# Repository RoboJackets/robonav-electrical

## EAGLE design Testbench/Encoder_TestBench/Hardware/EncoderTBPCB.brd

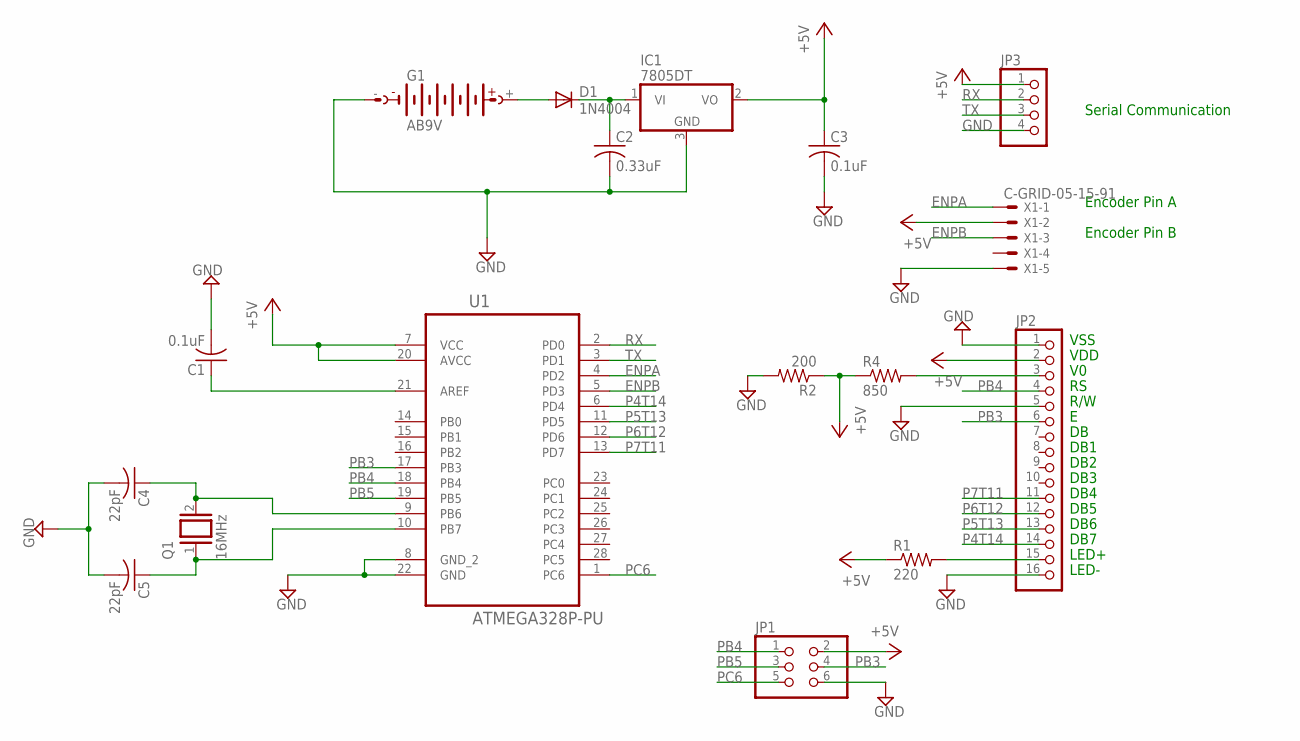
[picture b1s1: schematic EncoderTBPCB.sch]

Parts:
C1, C3: 0.1uF; C0603
C2: 0.33uF; C0603
C4, C5: 22pF; C0603
D1: 1N4004; DO41-10
G1: AB9V
IC1: 7805DT; TO252
JP1: PINHD-2X3; 2X03
JP2: PINHD-1X16; 1X16
JP3: PINHD-1X4; 1X04
Q1: 16MHz; QS
R1: 220; R0603
R2: 200; R0603
R4: 850; R0603
U1: ATMEGA328P-PU; DIP254P762X457-28
X1: C-GRID-05-15-91; 15-91-05

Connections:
CRYSTAL: C4.1, Q1.2, U1.9 (PB6)
ENPA: U1.4 (PD2), X1.1
ENPB: U1.5 (PD3), X1.3
GND: C1.2, C2.2, C3.2, C4.2, C5.2, G1.-, IC1.3 (GND), JP1.6, JP2.1, JP2.5, JP2.16, JP3.4, R2.2, U1.8 (GND_2), U1.22 (GND), X1.5
unnamed: JP2.15, R1.2
unnamed: C5.1, Q1.1, U1.10 (PB7)
unnamed: C1.1, U1.21 (AREF)
unnamed: D1.A, G1.+
unnamed: C2.1, D1.C, IC1.1 (VI)
P4T14: JP2.14, U1.6 (PD4)
P5T13: JP2.13, U1.11 (PD5)
P6T12: JP2.12, U1.12 (PD6)
P7T11: JP2.11, U1.13 (PD7)
PB3: JP1.4, JP2.6, U1.17 (PB3)
PB4: JP1.1, JP2.4, U1.18 (PB4)
PB5: JP1.3, U1.19 (PB5)
PC6: JP1.5, U1.1 (PC6)
RX: JP3.2, U1.2 (PD0)
TX: JP3.3, U1.3 (PD1)
VDD: C3.1, IC1.2 (VO), JP1.2, JP2.2, JP3.1, R1.1, R2.1, R4.1, U1.7 (VCC), U1.20 (AVCC), X1.2
VO: JP2.3, R4.2

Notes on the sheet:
VSS
VDD
R/W
DB1
DB2
DB3
DB4
DB5
DB6
DB7
LED+
LED-
Encoder Pin A
Encoder Pin B
Serial Communication

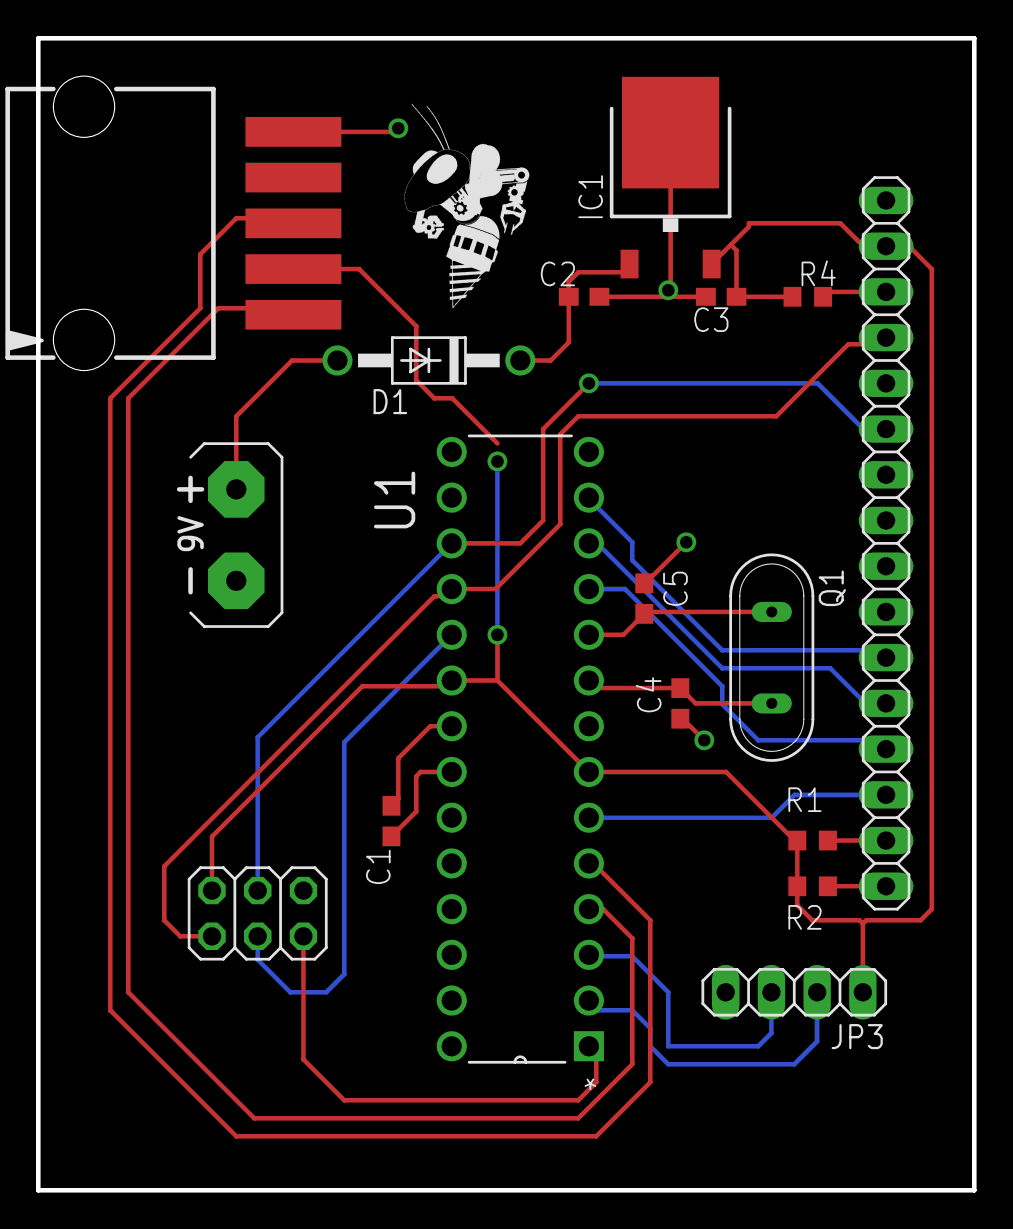
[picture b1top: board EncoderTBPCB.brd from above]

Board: 2 copper layers, 52.0 x 64.0 mm, 18 parts (0 on the bottom side), 21 nets.

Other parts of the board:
U$1: ROBOBUZZ_0.6X

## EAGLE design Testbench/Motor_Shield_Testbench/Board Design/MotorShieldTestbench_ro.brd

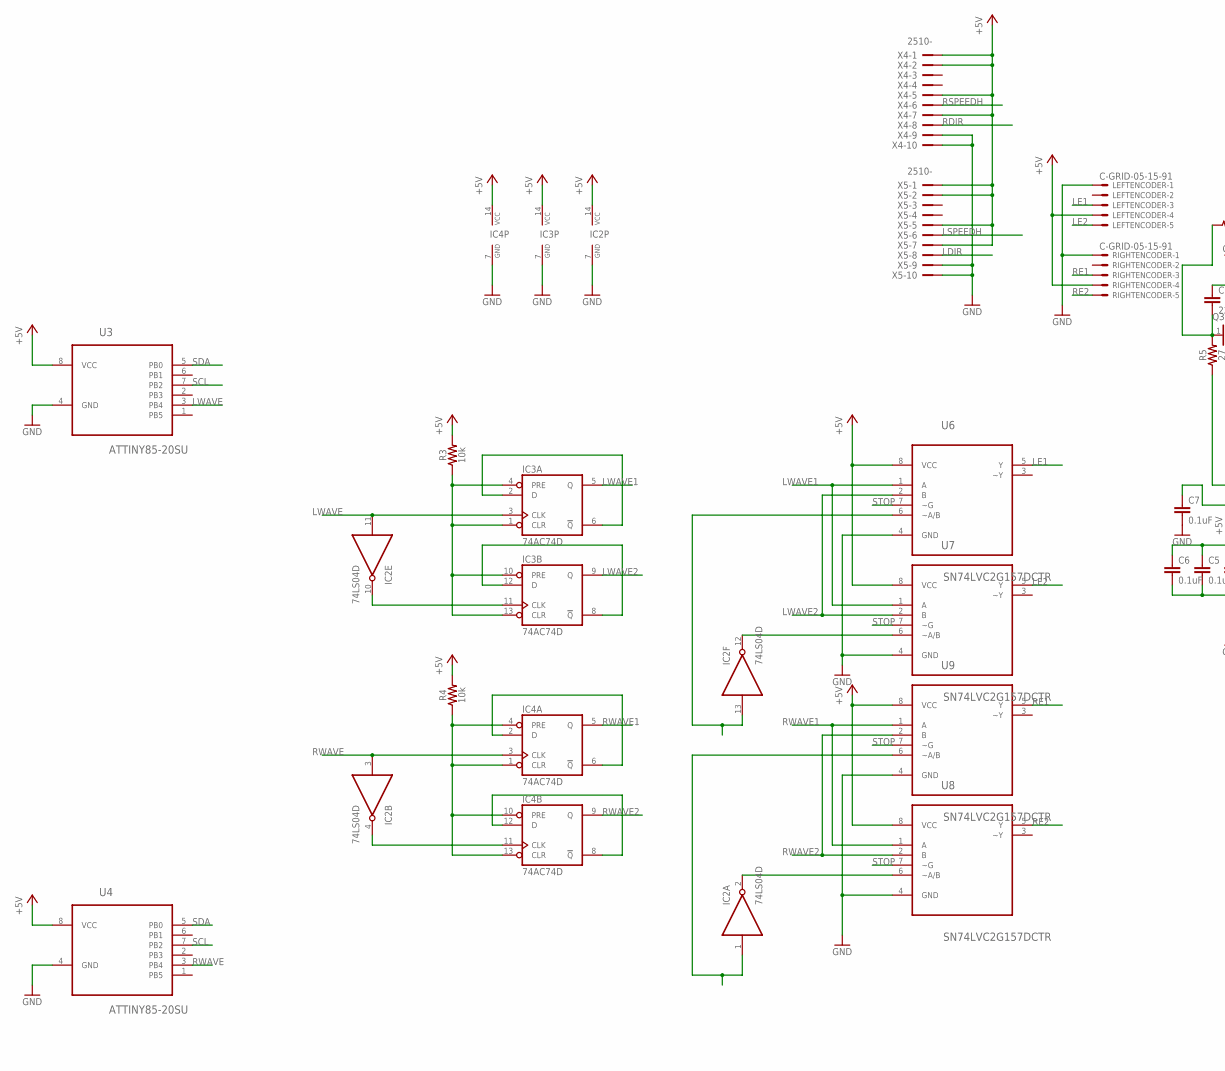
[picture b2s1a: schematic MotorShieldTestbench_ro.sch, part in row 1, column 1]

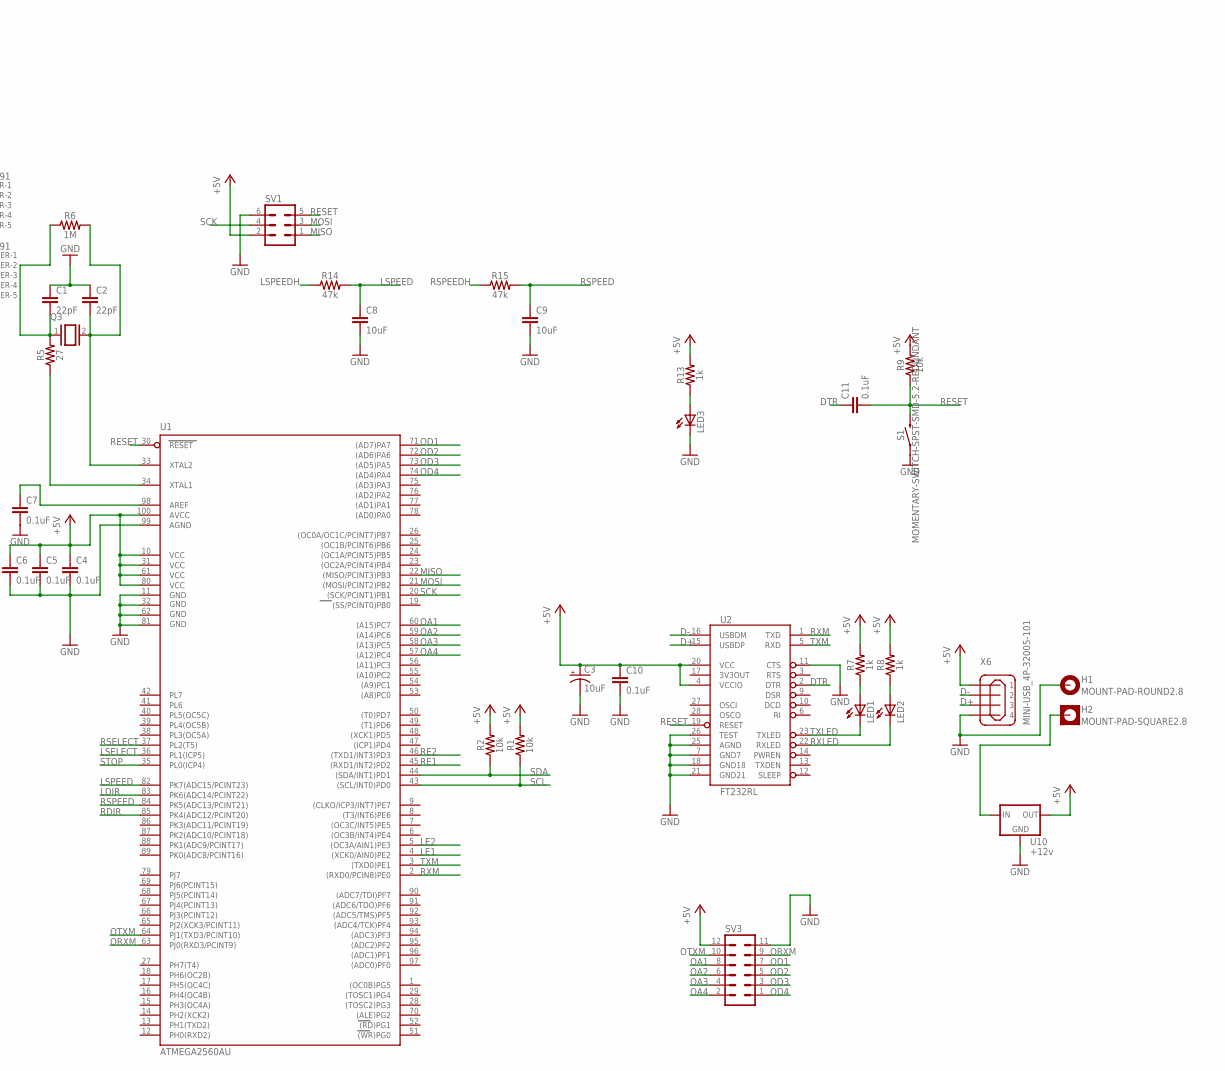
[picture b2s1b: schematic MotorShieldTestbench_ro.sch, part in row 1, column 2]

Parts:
C1, C2: 22pF; 0603
C3: 10uF; 0603-POLAR
C4, C5, C6, C7, C11: 0.1uF; 0603
C8, C9: 10uF; 0603
C10: 0.1uF; 0402
H1: MOUNT-PAD-ROUND2.8; 2,8-PAD
H2: MOUNT-PAD-SQUARE2.8; 2,8-PAD-SQUARE
IC2: 74LS04D; SO14
IC3, IC4: 74AC74D; SO14
LED1, LED2, LED3: LED_E; LED_1206
LEFTENCODER: C-GRID-05-15-91; 15-91-05
Q3: XTAL/S; QS
R1, R2, R3, R4, R9: 10k; 0603
R5: 27; 0603
R6: 1M; 0603
R7, R8, R13: 1k; 0603
R14, R15: 47k; 0603
RIGHTENCODER: C-GRID-05-15-91; 15-91-05
S1: MOMENTARY-SWITCH-SPST-SMD-5.2-REDUNDANT; TACTILE_SWITCH_SMD_5.2MM
SV1: MA03-2
SV3: MA06-2
U1: ATMEGA2560AU; TQFP100
U2: FT232RL; SSOP28DB
U3, U4: ATTINY85-20SU; SOIC127P798X216-8N
U6, U7, U8, U9: SN74LVC2G157DCTR; SOP65P400X130-8N
U10: +12v; TO-252
X4, X5: 2510-; PAK100/2500-10
X6: MINI-USB_4P-32005-101; 32005-101

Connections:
+5V: C3.+, C4.1, C5.1, C6.1, C10.1, IC2.14 (VCC), IC3.14 (VCC), IC4.14 (VCC), LEFTENCODER.4, R1.2, R2.2, R3.2, R4.2, R7.2, R8.2, R9.2, R13.2, RIGHTENCODER.4, SV1.2, SV3.12, U1.10 (VCC), U1.31 (VCC1), U1.61 (VCC2), U1.80 (VCC3), U1.100 (AVCC), U2.4 (VCCIO), U2.20 (VCC), U3.8 (VCC), U4.8 (VCC), U6.8 (VCC), U7.8 (VCC), U8.8 (VCC), U9.8 (VCC), U10.2 (OUT), X4.1, X4.2, X4.5, X4.7, X5.1, X5.2, X5.5, X5.7, X6.1
D+: U2.15 (USBDP), X6.3
D-: U2.16 (USBDM), X6.2
DTR: C11.1, U2.2 (DTR)
GND: C1.1, C2.1, C3.-, C4.2, C5.2, C6.2, C7.2, C8.2, C9.2, C10.2, H1.B2,8, IC2.7 (GND), IC3.7 (GND), IC4.7 (GND), LED3.C, LEFTENCODER.1, RIGHTENCODER.1, S1.1, S1.2 (1), SV1.6, SV3.11, U1.11 (GND), U1.32 (GND1), U1.62 (GND2), U1.81 (GND3), U1.99 (AGND), U2.7 (GND7), U2.11 (CTS), U2.18 (GND18), U2.21 (GND21), U2.25 (AGND), U2.26 (TEST), U3.4 (GND), U4.4 (GND), U6.4 (GND), U7.4 (GND), U8.4 (GND), U9.4 (GND), U10.3 (GND), X4.9, X4.10, X5.9, X5.10, X6.4
LDIR: U1.83 (PK6(ADC14/PCINT22)), X5.8
LE1: LEFTENCODER.3, U1.4 ((XCK0/AIN0)PE2), U6.5 (Y)
LE2: LEFTENCODER.5, U1.5 ((OC3A/AIN1)PE3), U7.5 (Y)
LSELECT: IC2.13 (I), U1.36 (PL1(ICP5)), U6.6 (~A/B)
LSPEED: C8.1, R14.2, U1.82 (PK7(ADC15/PCINT23))
LSPEEDH: R14.1, X5.6
LWAVE: IC2.11 (I), IC3.3 (CLK), U3.3 (PB4)
LWAVE1: IC3.5 (Q), U6.1 (A), U7.1 (A)
LWAVE2: IC3.9 (Q), U6.2 (B), U7.2 (B)
MISO: SV1.1, U1.22 ((MISO/PCINT3)PB3)
MOSI: SV1.3, U1.21 ((MOSI/PCINT2)PB2)
unnamed: IC3.2 (D), IC3.6 (!Q)
unnamed: IC2.2 (O), U8.6 (~A/B)
unnamed: IC3.8 (!Q), IC3.12 (D)
unnamed: IC4.2 (D), IC4.6 (!Q)
unnamed: IC4.8 (!Q), IC4.12 (D)
unnamed: IC2.12 (O), U7.6 (~A/B)
unnamed: IC4.1 (CLR), IC4.4 (PRE), IC4.10 (PRE), IC4.13 (CLR), R4.1
unnamed: IC3.1 (CLR), IC3.4 (PRE), IC3.10 (PRE), IC3.13 (CLR), R3.1
unnamed: IC2.4 (O), IC4.11 (CLK)
unnamed: R5.1, U1.34 (XTAL1)
unnamed: C2.2, Q3.2, R6.2, U1.33 (XTAL2)
unnamed: IC2.10 (O), IC3.11 (CLK)
unnamed: H2.B2,8, U10.1 (IN)
unnamed: C7.1, U1.98 (AREF)
unnamed: LED1.A, R7.1
unnamed: LED2.A, R8.1
unnamed: LED3.A, R13.1
unnamed: C1.2, Q3.1, R5.2, R6.1
OA1: SV3.8, U1.60 ((A15)PC7)
OA2: SV3.6, U1.59 ((A14)PC6)
OA3: SV3.4, U1.58 ((A13)PC5)
OA4: SV3.2, U1.57 ((A12)PC4)
OD1: SV3.7, U1.71 ((AD7)PA7)
OD2: SV3.5, U1.72 ((AD6)PA6)
OD3: SV3.3, U1.73 ((AD5)PA5)
OD4: SV3.1, U1.74 ((AD4)PA4)
ORXM: SV3.9, U1.63 (PJ0(RXD3/PCINT9))
OTXM: SV3.10, U1.64 (PJ1(TXD3/PCINT10))
RDIR: U1.85 (PK4(ADC12/PCINT20)), X4.8
RE1: RIGHTENCODER.3, U1.45 ((RXD1/INT2)PD2), U9.5 (Y)
RE2: RIGHTENCODER.5, U1.46 ((TXD1/INT3)PD3), U8.5 (Y)
RESET: C11.2, R9.1, S1.3 (2), S1.4 (2), SV1.5, U1.30 (RESET), U2.19 (RESET)
RSELECT: IC2.1 (I), U1.37 (PL2(T5)), U9.6 (~A/B)
RSPEED: C9.1, R15.2, U1.84 (PK5(ADC13/PCINT21))
RSPEEDH: R15.1, X4.6
RWAVE: IC2.3 (I), IC4.3 (CLK), U4.3 (PB4)
RWAVE1: IC4.5 (Q), U8.1 (A), U9.1 (A)
RWAVE2: IC4.9 (Q), U8.2 (B), U9.2 (B)
RXLED: LED2.C, U2.22 (RXLED)
RXM: U1.2 ((RXD0/PCIN8)PE0), U2.1 (TXD)
SCK: SV1.4, U1.20 ((SCK/PCINT1)PB1)
SCL: R1.1, U1.43 ((SCL/INT0)PD0), U3.7 (PB2), U4.7 (PB2)
SDA: R2.1, U1.44 ((SDA/INT1)PD1), U3.5 (PB0), U4.5 (PB0)
STOP: U1.35 (PL0(ICP4)), U6.7 (~G), U7.7 (~G), U8.7 (~G), U9.7 (~G)
TXLED: LED1.C, U2.23 (TXLED)
TXM: U1.3 ((TXD0)PE1), U2.5 (RXD)

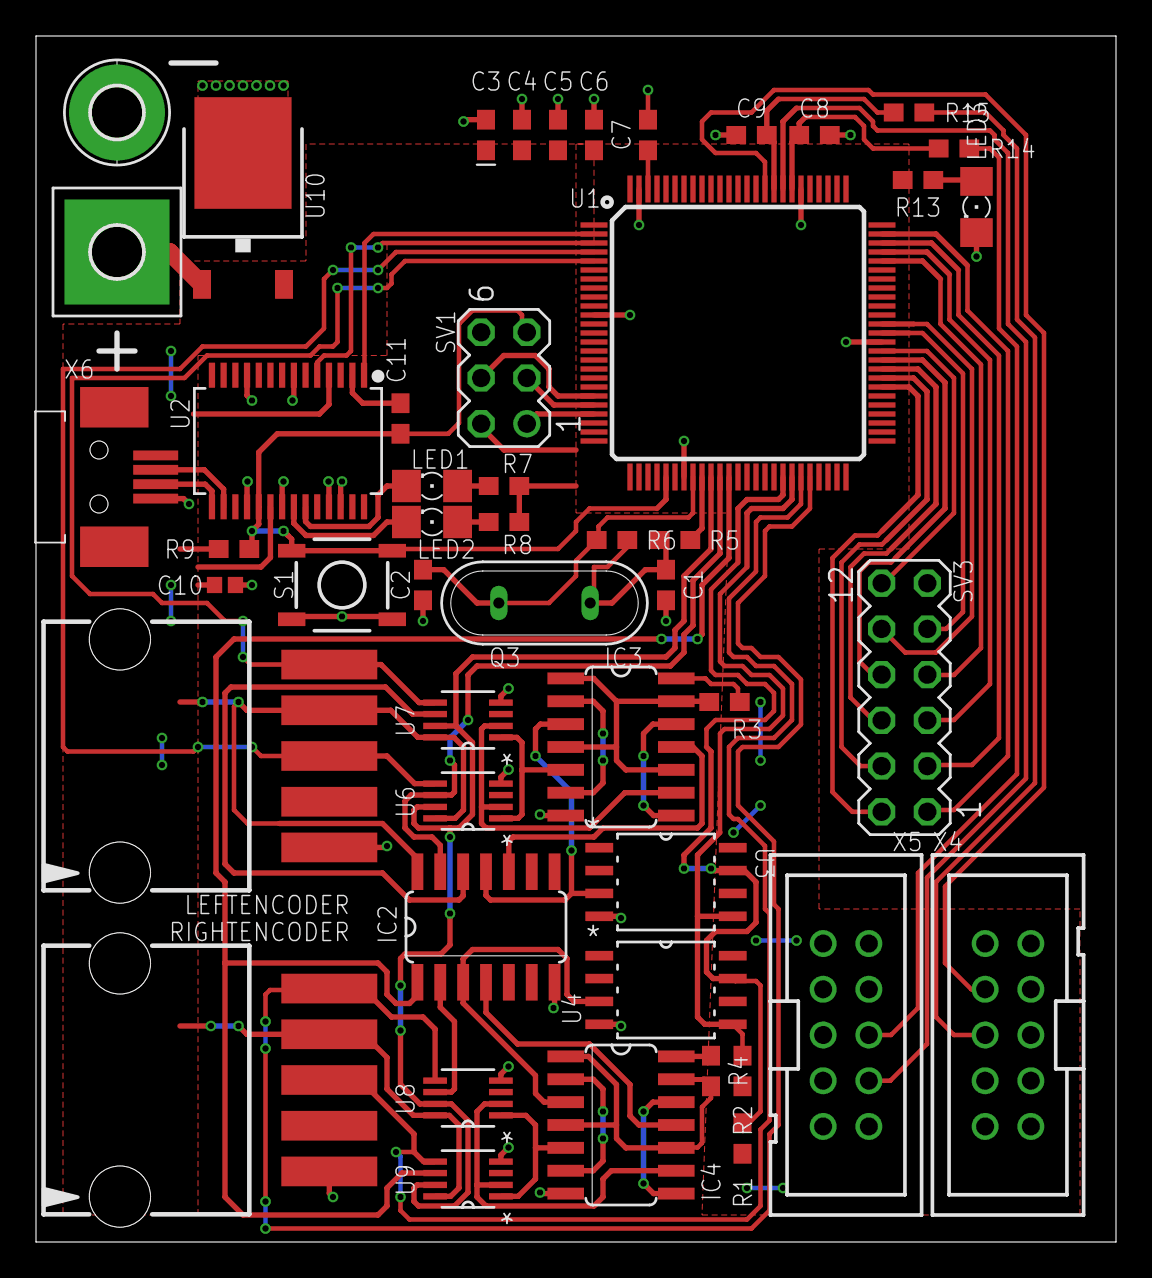
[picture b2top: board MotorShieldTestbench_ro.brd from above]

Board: 2 copper layers, 60.0 x 67.0 mm, 49 parts (0 on the bottom side), 62 nets.

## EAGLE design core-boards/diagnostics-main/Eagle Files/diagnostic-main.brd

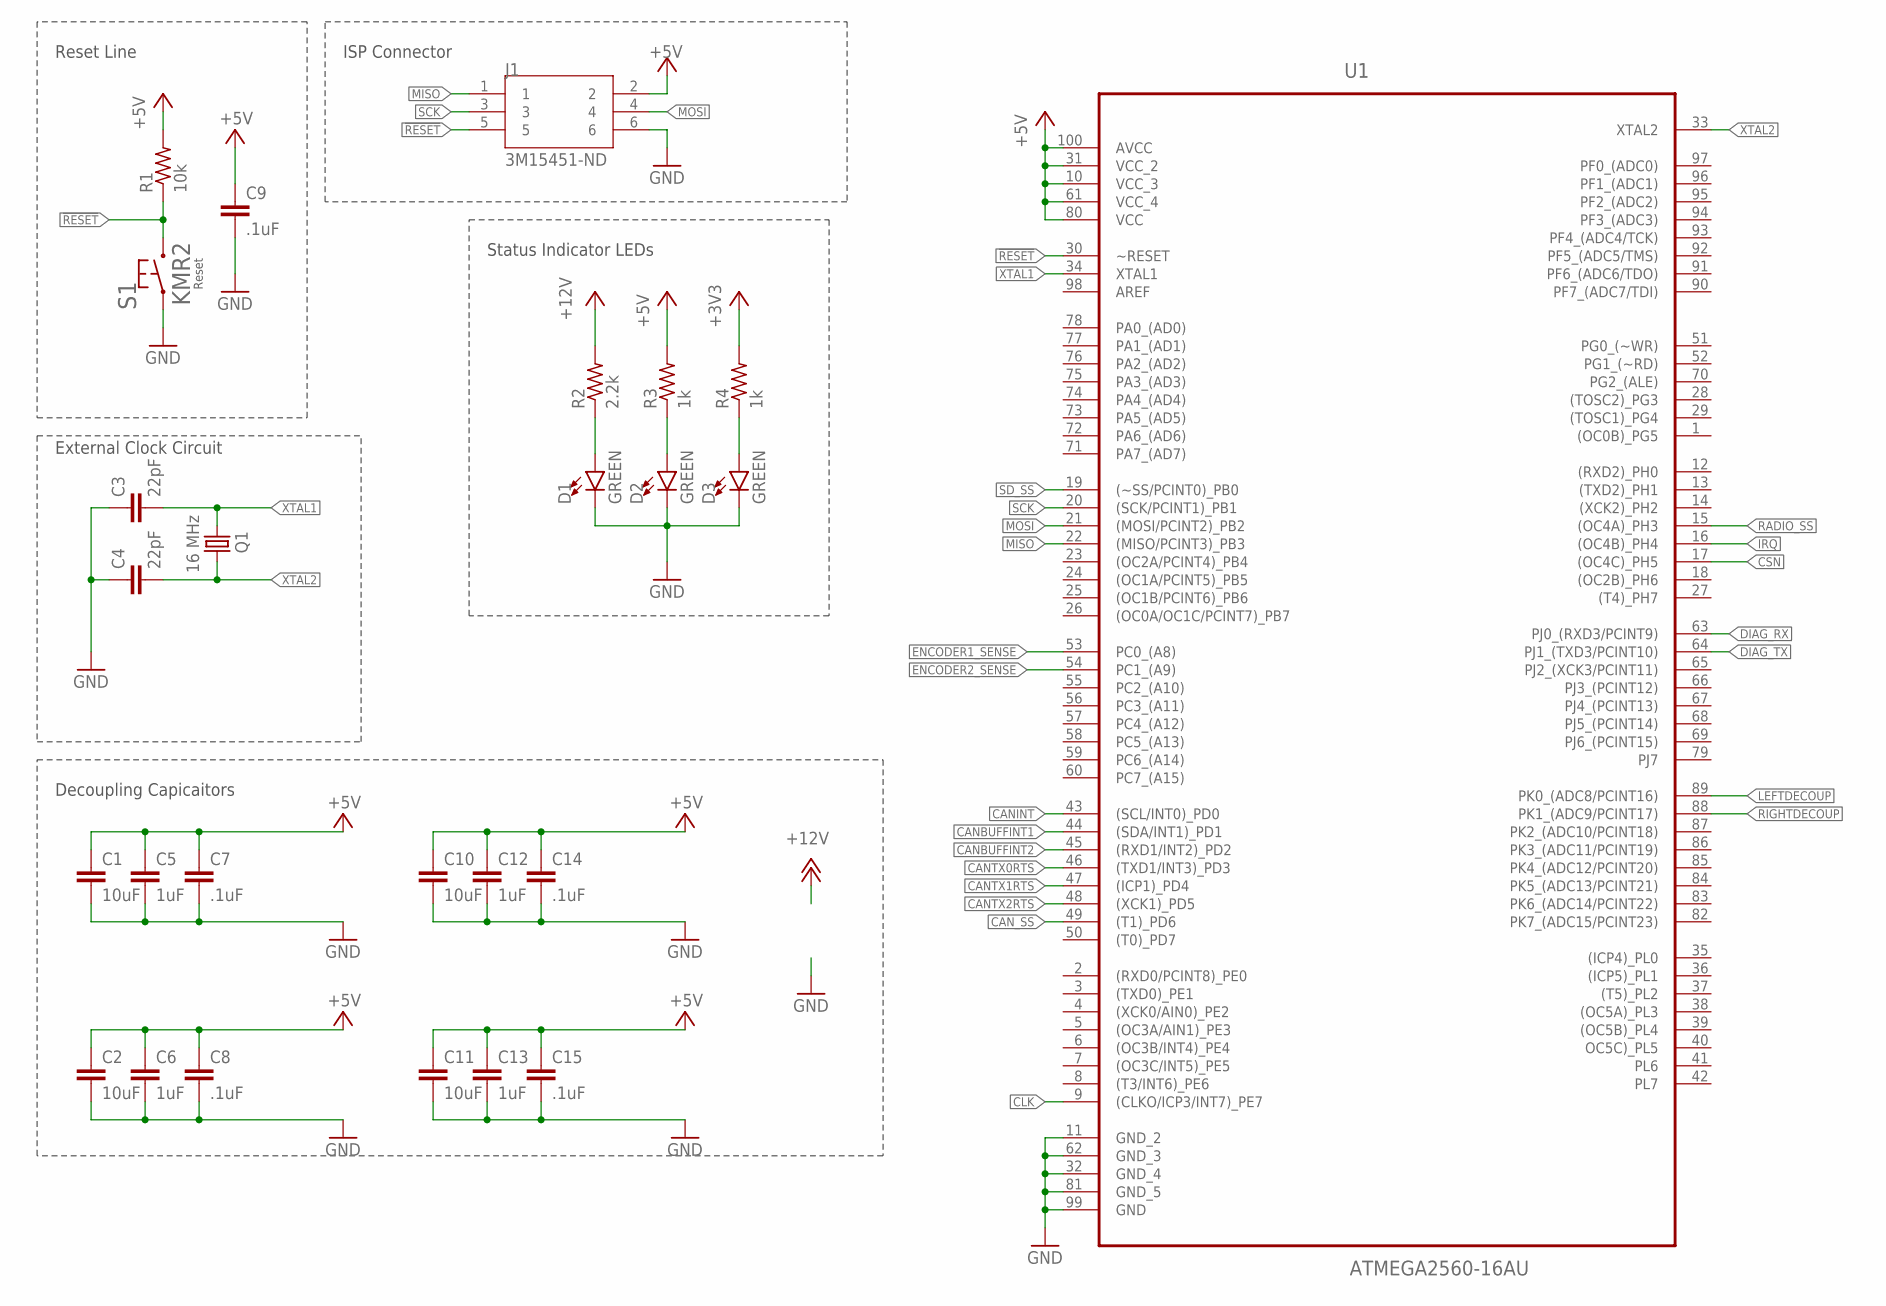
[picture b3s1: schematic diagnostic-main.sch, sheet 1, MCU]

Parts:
C1, C2, C10, C11: 10uF; C0805
C3, C4: 22pF; C0603
C5, C6, C12, C13: 1uF; C0603
C7, C8, C9, C14, C15: .1uF; C0603
D1, D2, D3: GREEN; LED-0603
J1: 3M15451-ND; 3M_30306-6002HB
Q1: 16 MHz; CSM-7X-DU
R1: 10k; R0603
R2: 2.2k; R0603
R3, R4: 1k; R0603
S1: KMR2
U1: ATMEGA2560-16AU; QFP50P1600X1600X120-100N

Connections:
3V3_LED_R: D3.A, R4.1
5V_LED_R: D2.A, R3.1
12V_LED_R: D1.A, R2.1
!RESET: J1.5, R1.1, S1.2.1 (2), S1.2.2 (2), U1.30 (~RESET)
+3V3: R4.2; also elsewhere on the board
+5V: C1.1, C2.1, C5.1, C6.1, C7.1, C8.1, C9.1, C10.1, C11.1, C12.1, C13.1, C14.1, C15.1, J1.2, R1.2, R3.2, U1.10 (VCC_3), U1.31 (VCC_2), U1.61 (VCC_4), U1.80 (VCC), U1.100 (AVCC); also elsewhere on the board
+12V: R2.2; also elsewhere on the board
CANBUFFINT1: U1.44 ((SDA/INT1)_PD1); also elsewhere on the board
CANBUFFINT2: U1.45 ((RXD1/INT2)_PD2); also elsewhere on the board
CANINT: U1.43 ((SCL/INT0)_PD0); also elsewhere on the board
CANTX0RTS: U1.46 ((TXD1/INT3)_PD3); also elsewhere on the board
CANTX1RTS: U1.47 ((ICP1)_PD4); also elsewhere on the board
CANTX2RTS: U1.48 ((XCK1)_PD5); also elsewhere on the board
CAN_SS: U1.49 ((T1)_PD6); also elsewhere on the board
CLK: U1.9 ((CLKO/ICP3/INT7)_PE7); also elsewhere on the board
CSN: U1.17 ((OC4C)_PH5); also elsewhere on the board
DIAG_RX: U1.63 (PJ0_(RXD3/PCINT9)); also elsewhere on the board
DIAG_TX: U1.64 (PJ1_(TXD3/PCINT10)); also elsewhere on the board
ENCODER1_SENSE: U1.53 (PC0_(A8)); also elsewhere on the board
ENCODER2_SENSE: U1.54 (PC1_(A9)); also elsewhere on the board
GND: C1.2, C2.2, C3.1, C4.1, C5.2, C6.2, C7.2, C8.2, C9.2, C10.2, C11.2, C12.2, C13.2, C14.2, C15.2, D1.C, D2.C, D3.C, J1.6, S1.1.1 (1), S1.1.2 (1), U1.11 (GND_2), U1.32 (GND_4), U1.62 (GND_3), U1.81 (GND_5), U1.99 (GND); also elsewhere on the board
IRQ: U1.16 ((OC4B)_PH4); also elsewhere on the board
LEFTDECOUP: U1.89 (PK0_(ADC8/PCINT16)); also elsewhere on the board
MISO: J1.1, U1.22 ((MISO/PCINT3)_PB3); also elsewhere on the board
MOSI: J1.4, U1.21 ((MOSI/PCINT2)_PB2); also elsewhere on the board
RADIO_SS: U1.15 ((OC4A)_PH3); also elsewhere on the board
RIGHTDECOUP: U1.88 (PK1_(ADC9/PCINT17)); also elsewhere on the board
SCK: J1.3, U1.20 ((SCK/PCINT1)_PB1); also elsewhere on the board
SD_SS: U1.19 ((~SS/PCINT0)_PB0); also elsewhere on the board
XTAL1: C3.2, Q1.1, U1.34 (XTAL1)
XTAL2: C4.2, Q1.2, U1.33 (XTAL2)

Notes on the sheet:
Reset Line
External Clock Circuit
Decoupling Capicaitors
ISP Connector
Status Indicator LEDs

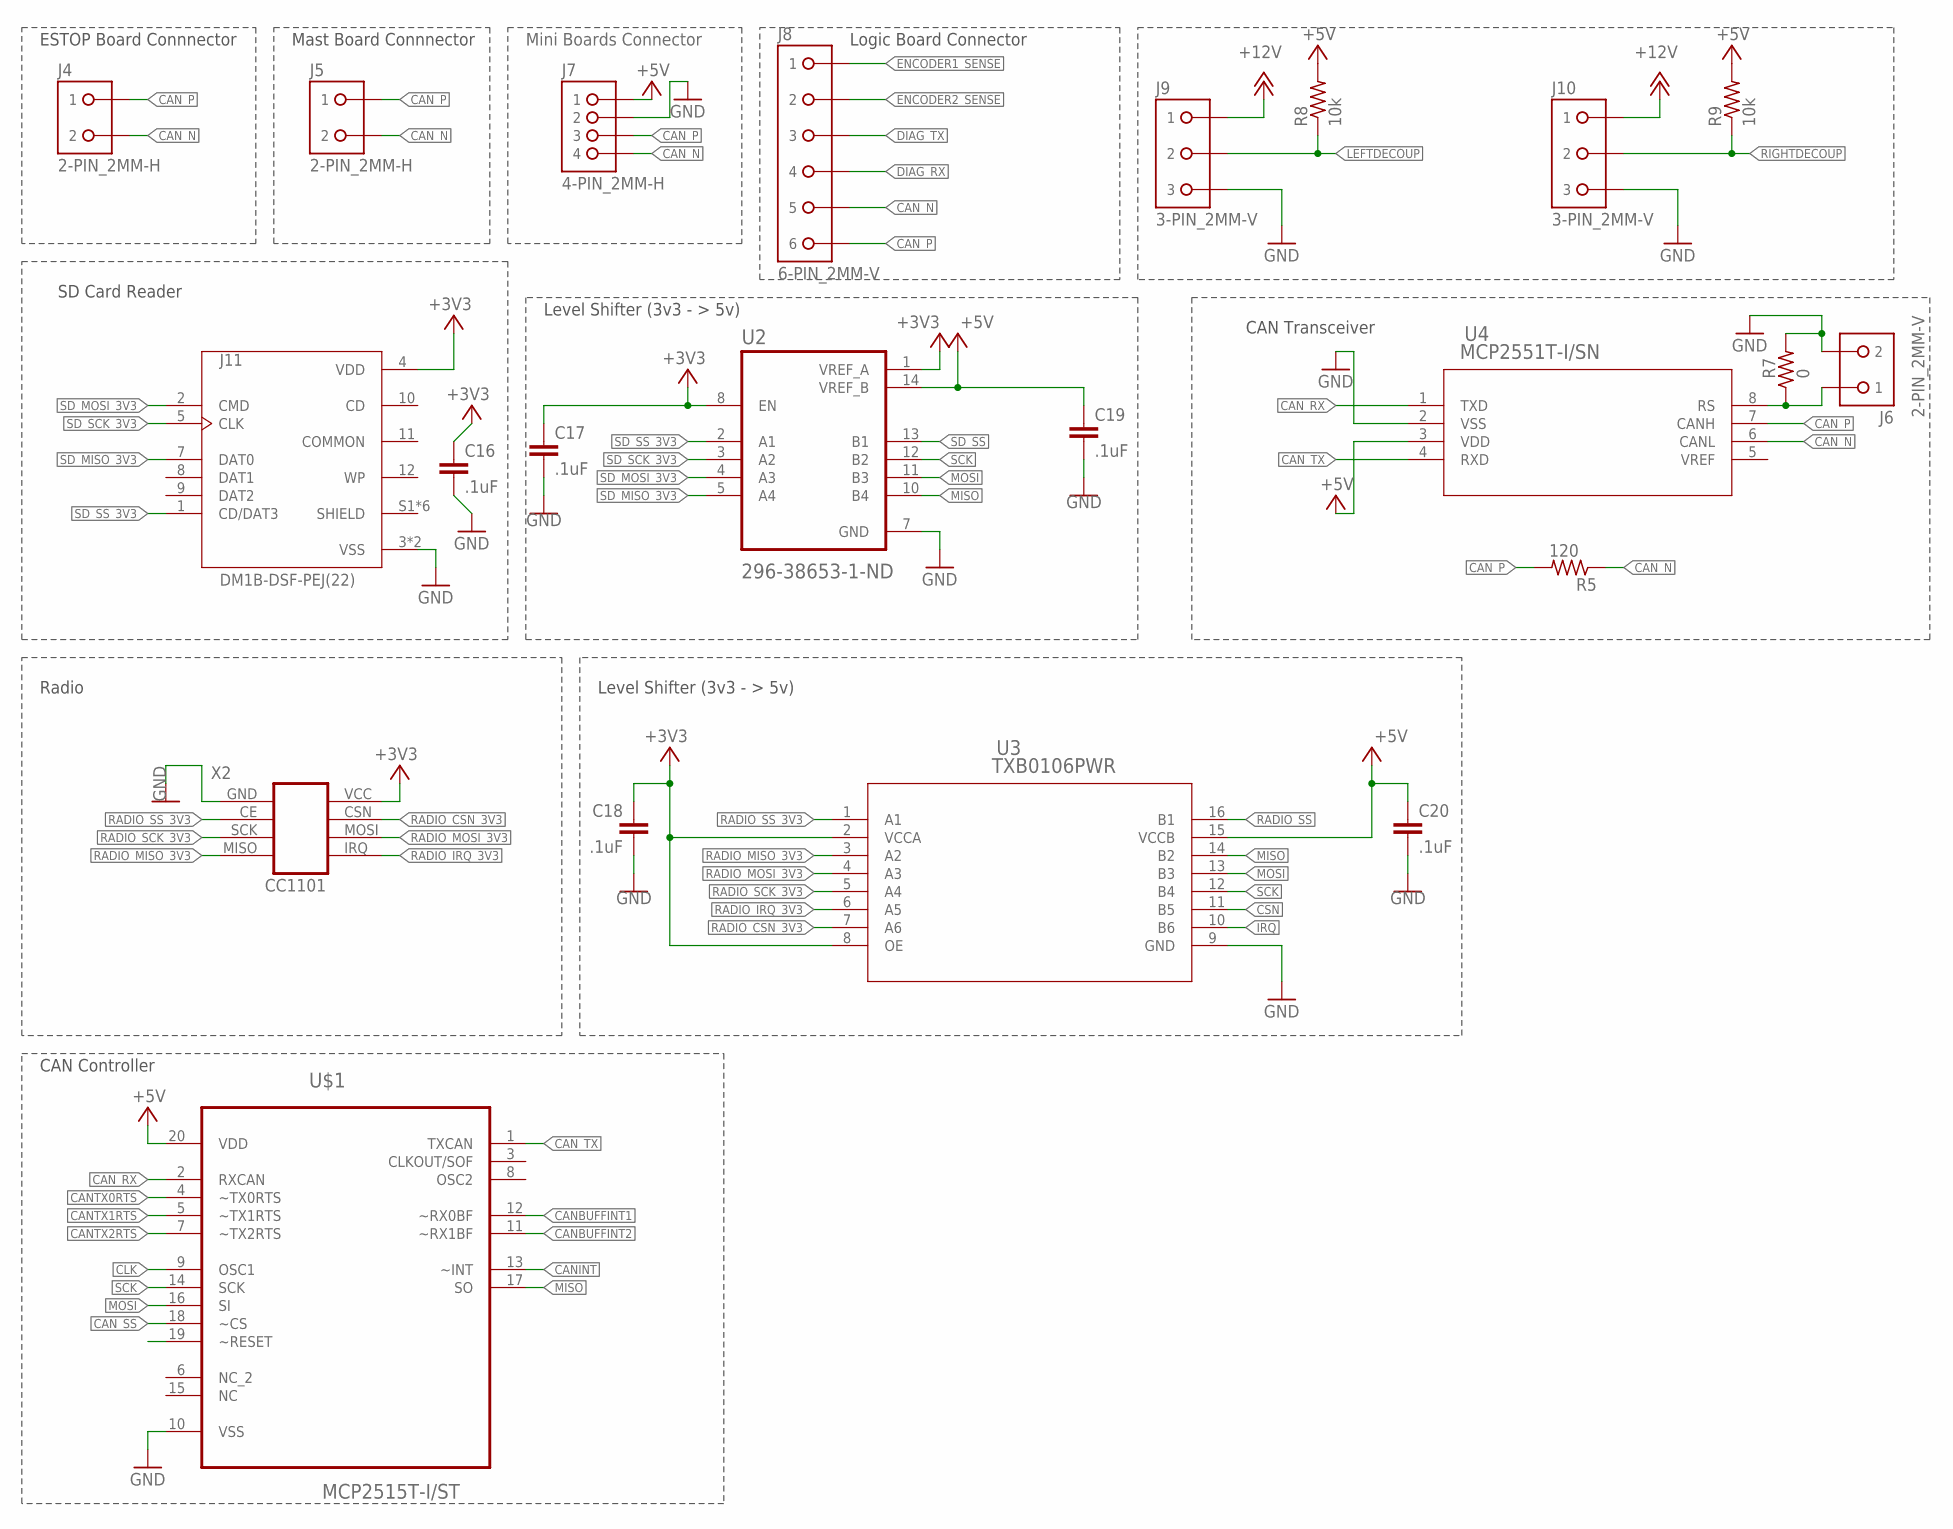
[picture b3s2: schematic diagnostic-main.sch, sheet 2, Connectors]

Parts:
C16, C17, C18, C19, C20: .1uF; C0603
J4, J5: 2-PIN_2MM-H; 2MM-2-H
J6: 2-PIN_2MM-V; 2MM-2-V
J7: 4-PIN_2MM-H; 2MM-4-H
J8: 6-PIN_2MM-V; 2MM-6-V
J9, J10: 3-PIN_2MM-V; 2MM-3-V
J11: DM1B-DSF-PEJ(22); JST_DM1B-DSF-PEJ(22)
R5: 120; R0603
R7: 0; R0603
R8, R9: 10k; R0603
U2: 296-38653-1-ND; SOP65P640X120-14N
U3: TXB0106PWR; PW16
U4: MCP2551T-I/SN; SOIC8-N_MC
U$1: MCP2515T-I/ST; SOP65P640X110-20N
X2: CC1101; NRF24L01+PA+LNA

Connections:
+3V3: C16.1, C17.1, C18.1, J11.4 (VDD), U2.1 (VREF_A), U2.8 (EN), U3.2 (VCCA), U3.8 (OE), X2.VCC; also elsewhere on the board
+5V: C19.1, C20.1, J7.1, R8.2, R9.2, U2.14 (VREF_B), U3.15 (VCCB), U4.3 (VDD), U$1.20 (VDD); also elsewhere on the board
+12V: J9.1, J10.1; also elsewhere on the board
CANBUFFINT1: U$1.12 (~RX0BF); also elsewhere on the board
CANBUFFINT2: U$1.11 (~RX1BF); also elsewhere on the board
CANINT: U$1.13 (~INT); also elsewhere on the board
CANTX0RTS: U$1.4 (~TX0RTS); also elsewhere on the board
CANTX1RTS: U$1.5 (~TX1RTS); also elsewhere on the board
CANTX2RTS: U$1.7 (~TX2RTS); also elsewhere on the board
CAN_N: J4.2, J5.2, J7.4, J8.5, R5.1, U4.6 (CANL)
CAN_P: J4.1, J5.1, J7.3, J8.6, R5.2, U4.7 (CANH)
CAN_RX: U4.1 (TXD), U$1.2 (RXCAN)
CAN_SS: U$1.18 (~CS); also elsewhere on the board
CAN_TX: U4.4 (RXD), U$1.1 (TXCAN)
CLK: U$1.9 (OSC1); also elsewhere on the board
CSN: U3.11 (B5); also elsewhere on the board
DIAG_RX: J8.4; also elsewhere on the board
DIAG_TX: J8.3; also elsewhere on the board
ENCODER1_SENSE: J8.1; also elsewhere on the board
ENCODER2_SENSE: J8.2; also elsewhere on the board
GND: C16.2, C17.2, C18.2, C19.2, C20.2, J6.2, J7.2, J9.3, J10.3, J11.3 (VSS), J11.6 (VSS), R7.2, U2.7 (GND), U3.9 (GND), U4.2 (VSS), U$1.10 (VSS), X2.GND; also elsewhere on the board
IRQ: U3.10 (B6); also elsewhere on the board
LEFTDECOUP: J9.2, R8.1; also elsewhere on the board
MISO: U2.10 (B4), U3.14 (B2), U$1.17 (SO); also elsewhere on the board
MOSI: U2.11 (B3), U3.13 (B3), U$1.16 (SI); also elsewhere on the board
RADIO_CSN_3V3: U3.7 (A6), X2.CSN
RADIO_IRQ_3V3: U3.6 (A5), X2.IRQ
RADIO_MISO_3V3: U3.3 (A2), X2.MISO
RADIO_MOSI_3V3: U3.4 (A3), X2.MOSI
RADIO_SCK_3V3: U3.5 (A4), X2.SCK
RADIO_SS: U3.16 (B1); also elsewhere on the board
RADIO_SS_3V3: U3.1 (A1), X2.CE
RIGHTDECOUP: J10.2, R9.1; also elsewhere on the board
RS: J6.1, R7.1, U4.8 (RS)
SCK: U2.12 (B2), U3.12 (B4), U$1.14 (SCK); also elsewhere on the board
SD_MISO_3V3: J11.7 (DAT0), U2.5 (A4)
SD_MOSI_3V3: J11.2 (CMD), U2.4 (A3)
SD_SCK_3V3: J11.5 (CLK), U2.3 (A2)
SD_SS: U2.13 (B1); also elsewhere on the board
SD_SS_3V3: J11.1 (CD/DAT3), U2.2 (A1)

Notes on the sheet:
ESTOP Board Connnector
SD Card Reader
Level Shifter (3v3 - > 5v)
Logic Board Connector
Mini Boards Connector
CAN Transceiver
Radio
Mast Board Connnector
CAN Controller

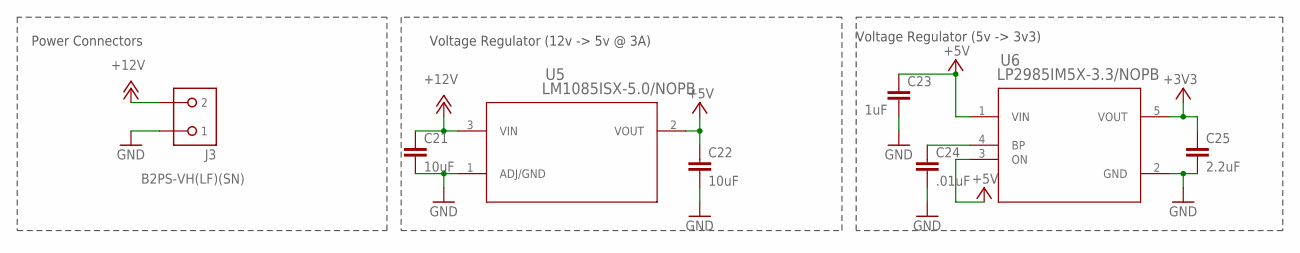
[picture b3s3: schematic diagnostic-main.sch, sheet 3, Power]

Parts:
C21, C22: 10uF; C0805
C23: 1uF; C0603
C24: .01uF; C0603
C25: 2.2uF; C0603
J3: B2PS-VH(LF)(SN); B2PS-CENTERED
U5: LM1085ISX-5.0/NOPB; TS3B
U6: LP2985IM5X-3.3/NOPB; MF05A

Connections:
+3V3: C25.1, U6.5 (VOUT); also elsewhere on the board
+5V: C22.1, C23.1, U5.2 (VOUT), U6.1 (VIN), U6.3 (ON); also elsewhere on the board
+12V: C21.1, J3.2, U5.3 (VIN); also elsewhere on the board
GND: C21.2, C22.2, C23.2, C24.2, C25.2, J3.1, U5.1 (ADJ/GND), U6.2 (GND); also elsewhere on the board
unnamed: C24.1, U6.4 (BP)

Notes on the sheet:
Voltage Regulator (12v -> 5v @ 3A)
Voltage Regulator (5v -> 3v3)
Power Connectors

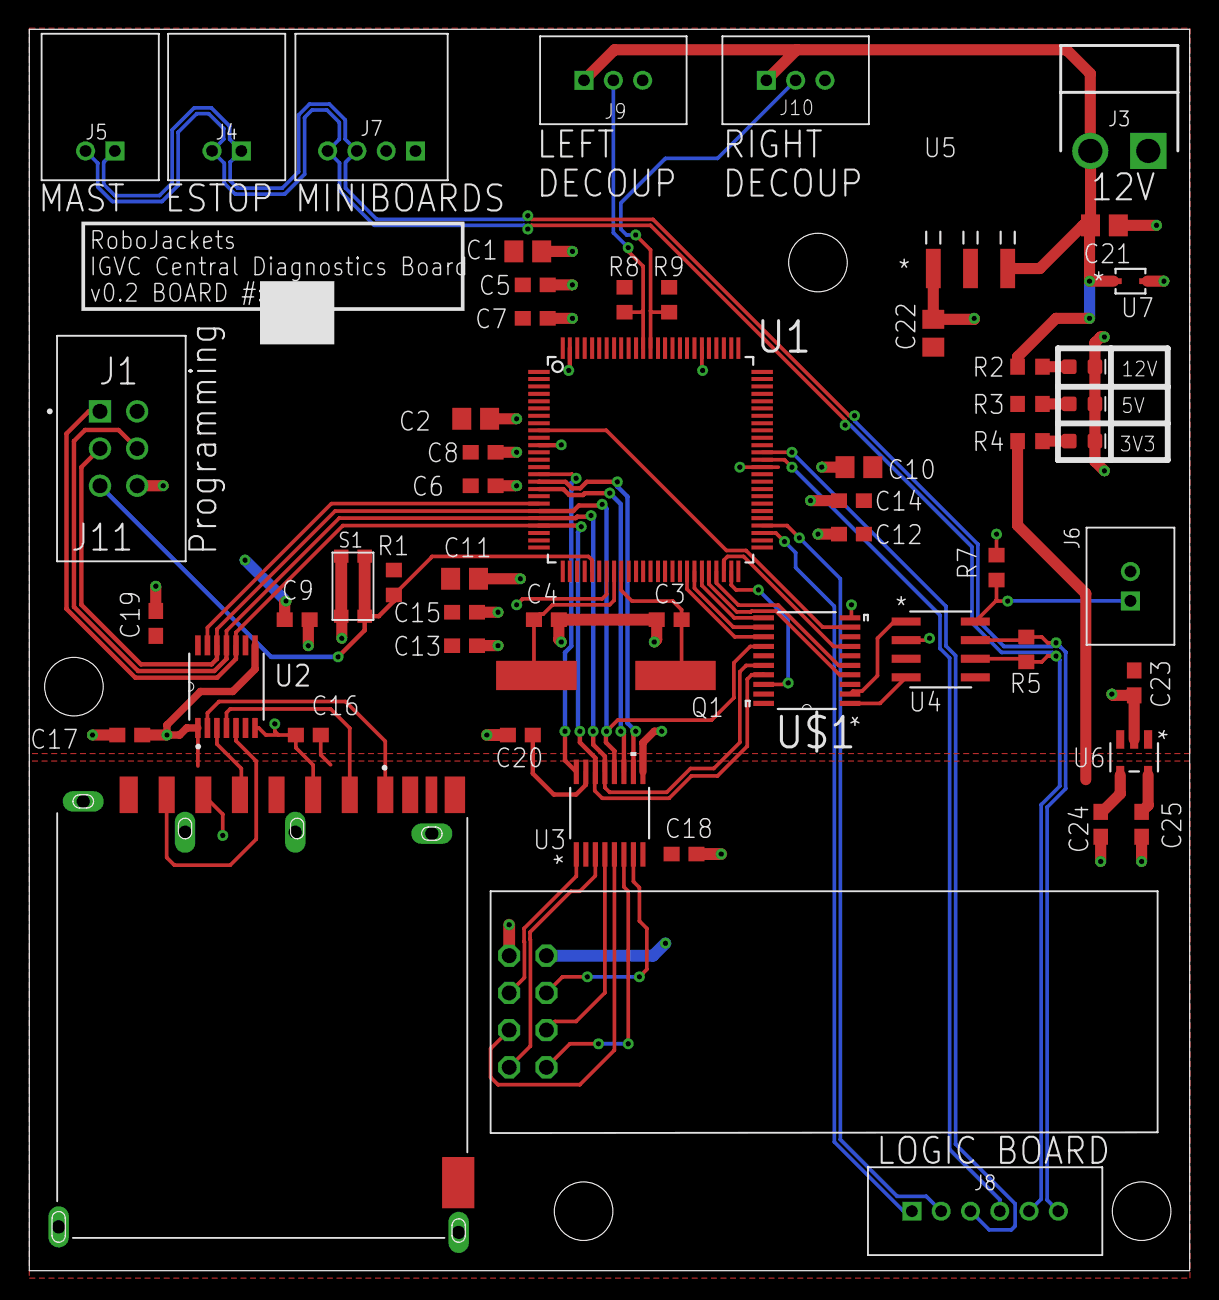
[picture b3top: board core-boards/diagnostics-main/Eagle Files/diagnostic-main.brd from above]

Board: 2 copper layers, 79.2 x 84.8 mm, 57 parts (0 on the bottom side), 47 nets.

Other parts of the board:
U7: D5V0L1B2WS-7; SOD323

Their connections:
+12V: U7.1; also elsewhere on the board
GND: U7.2; also elsewhere on the board

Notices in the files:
parts and their libraries:
SparkFun-Capacitors: Licensing: Creative Commons ShareAlike 4.0 International - https://creativecommons.org/licenses/by-sa/4.0
